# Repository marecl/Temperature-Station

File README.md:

# Temperature Station  
## I made this project for my father who needed to log activity of central heater  

Please use PCF8563_JSON version.  
I2C expander is ATmega board which will extend amount of sensors that can be connected (WIP).  

If there is Error[500] use another browser (8563 donsent work with Edge but DS32321 does idk why)  
	
		!!!TODO!!!  

	Main sketch:  
		1. Add SSL support (including login page)  
		2. WWW based updater  
		3. Automatic daylight saving  
		4. Encrypt WiFi password   
		5. Set date and time on the webpage  
		6. Save each file as JSON and show as CSV  
		7. SettingsGenerator for everything but sensors

	Czas.h library:  
		1. Return actual date and time as epoch  

	Hardware:   
		1. Make full-SMD version (without NodeMCU, just ESP-12E)

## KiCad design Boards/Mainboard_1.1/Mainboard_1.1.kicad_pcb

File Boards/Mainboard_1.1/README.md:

First version.
Single sided.
Requires retracing some SD lines which were connected to GPIO9&10.
No i2c breakout.

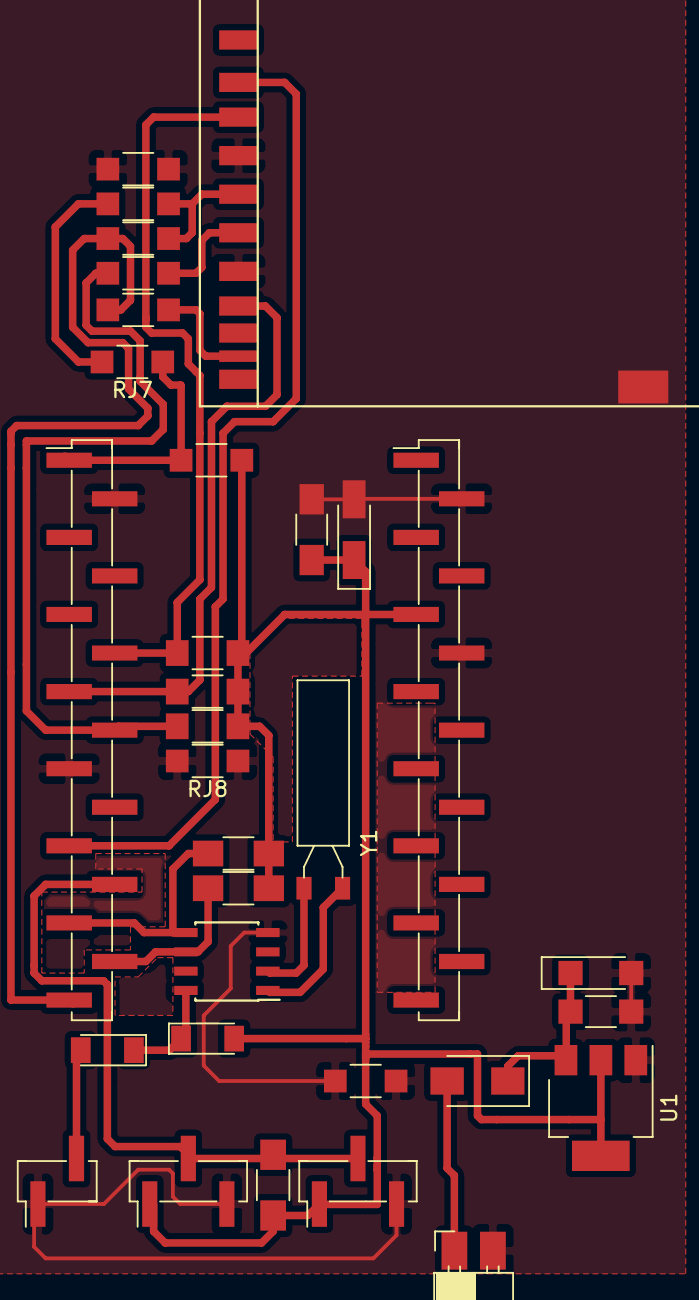
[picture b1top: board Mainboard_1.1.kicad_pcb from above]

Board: 2 copper layers, 32 parts (0 on the bottom side), 18 nets.

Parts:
C1, C3: 10nF; C_1206_HandSoldering
C2, C4: 10uF; CP_Tantalum_Case-A_EIA-3216-18_Hand
D1, D3: 1N4148; D_MiniMELF
D2: 1N4007; D_SMA
J1, J5: CONN_01X03; Pin_Header_Straight_1x03_Pitch2.54mm_SMD_Pin1Left
J2, J3: CONN_01X15; Pin_Header_Straight_1x15_Pitch2.54mm_SMD_Pin1Left
J4: SD_Card; SDCARD-STANDARD
J6: CONN_01X02; Pin_Header_Straight_1x02_Pitch2.54mm_SMD_Pin1Left
J7: CONN_01X02; Socket_Strip_Angled_1x02_Pitch2.54mm
R1, R2, R3, R4: 10k; R_1206_HandSoldering
R5, R6, R7: 4k7; R_1206_HandSoldering
RJ1, RJ2, RJ3, RJ4, RJ5, RJ6, RJ7, RJ8: 0; R_1206_HandSoldering
U1: LM1117-3.3; SOT-223-3Lead_TabPin2
U2: PCF8563; SOIC-8_3.9x4.9mm_Pitch1.27mm
Y1: Crystal; Crystal_AT310_d3.0mm_l10.0mm_Horizontal

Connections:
1wire: J1.2, J2.12, J5.2, R5.2
3V3: C3.1, C4.1, D1.2, J1.1, J2.1, J3.5, J4.4, J5.1, R1.1, R2.1, R3.1, R4.1, R5.1, R6.1, R7.1, RJ2.1, RJ2.2, RJ3.1, RJ3.2, RJ7.1, RJ7.2, U1.2
CS: J2.11, J4.1
GND: C1.2, C2.2, C3.2, C4.2, J1.3, J2.2, J2.9, J3.2, J3.6, J4.3, J4.6, J4.12, J5.3, J6.1, J7.2, RJ4.1, RJ4.2, RJ6.1, RJ6.2, RJ8.1, RJ8.2, U1.1, U2.4
MISO: J2.7, J4.7, R2.2
MOSI: J2.6, J4.2, R1.2
unnamed: C1.1, C2.1, D2.1, U1.3
unnamed: D1.1, D3.1, U2.8
unnamed: D2.2, J7.1
unnamed: D3.2, J6.2
unnamed: J2.8, R3.2, RJ1.1
unnamed: J4.10, RJ5.2
unnamed: U2.1, Y1.1
unnamed: U2.2, Y1.2
SCK: J4.5, RJ1.2
SCL: J2.14, R7.2, U2.6
SDA: J2.13, R6.2, U2.5
SD_D: J2.15, R4.2, RJ5.1

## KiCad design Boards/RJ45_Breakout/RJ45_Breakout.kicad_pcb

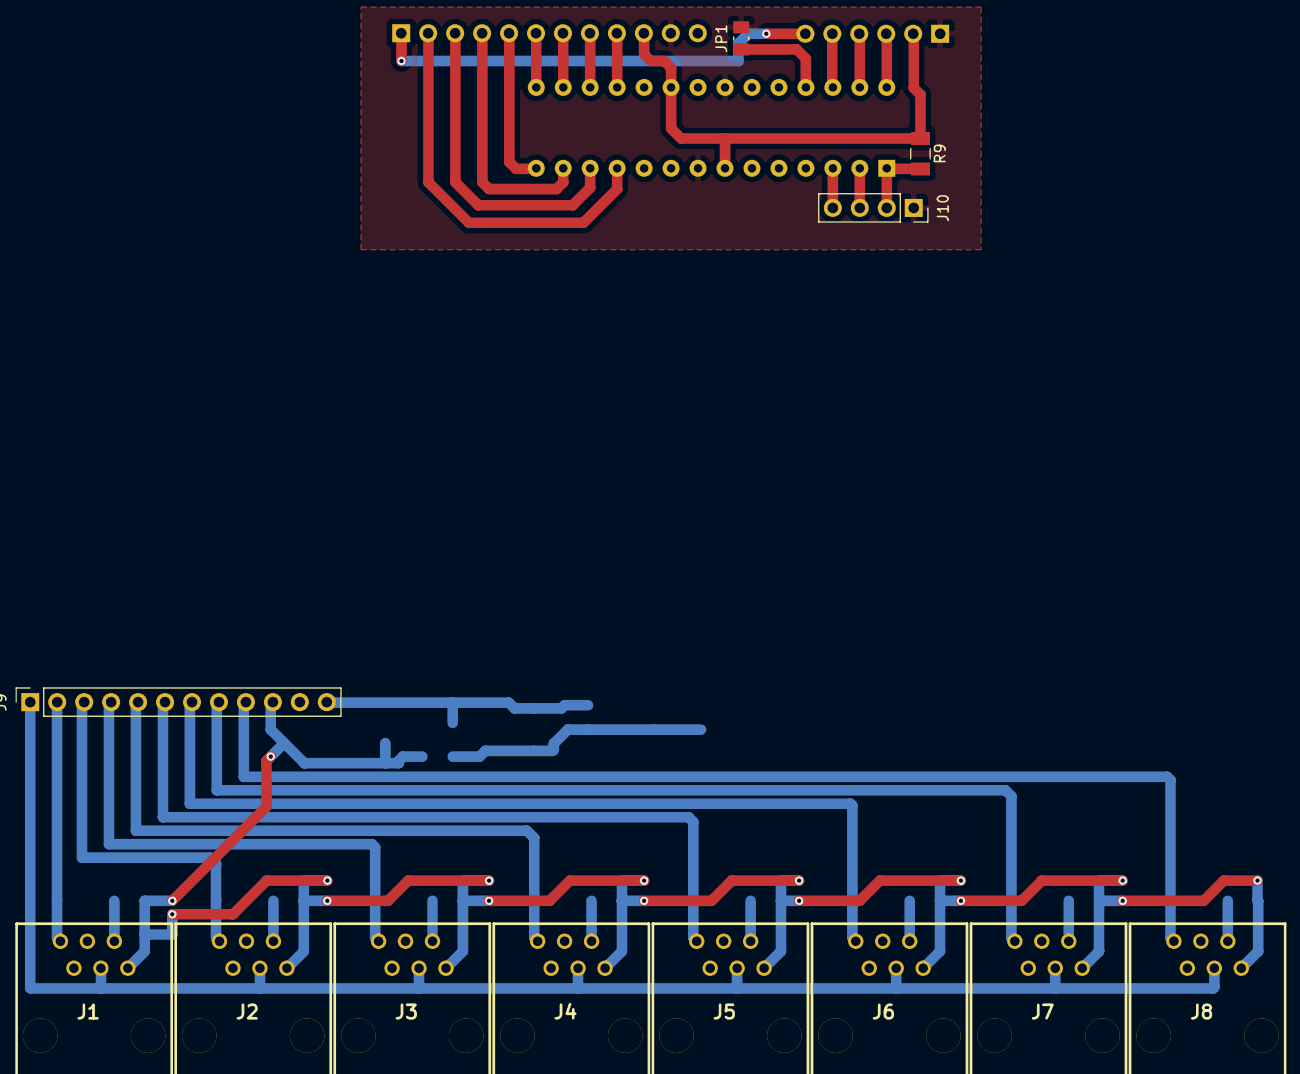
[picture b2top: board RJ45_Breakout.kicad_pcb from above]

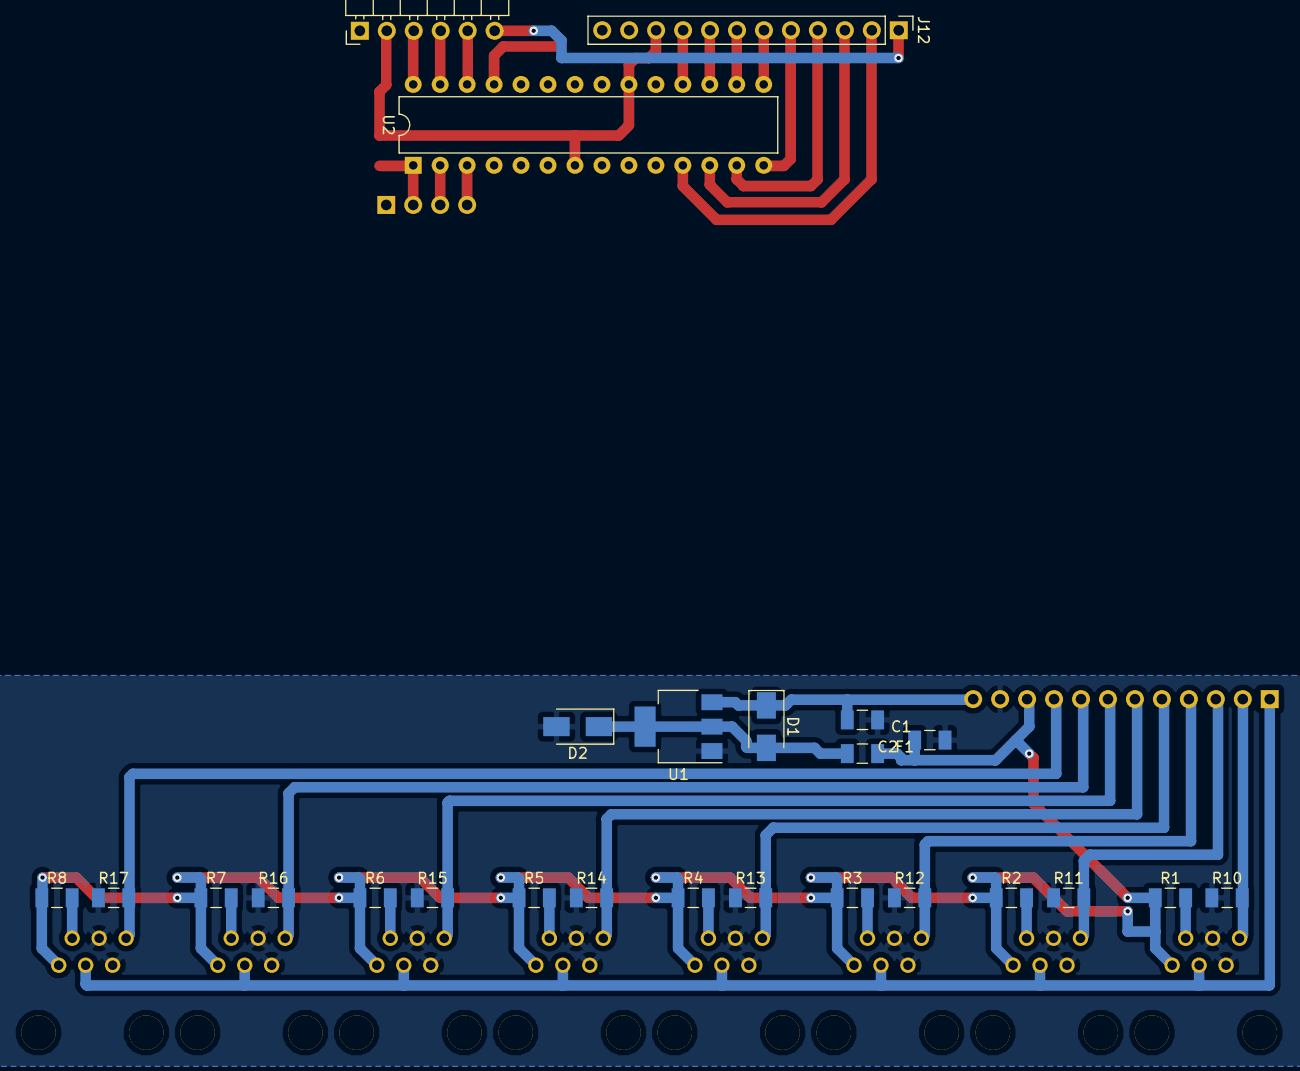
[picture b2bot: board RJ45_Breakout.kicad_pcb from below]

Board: 2 copper layers, 37 parts (25 on the bottom side), 28 nets.

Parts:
C1, C2: 100nF; C_1206_3216Metric
D1, D2: 1N4007; D_SMA
F1: 500mA; Fuse_1206_3216Metric
J1, J2, J3, J4, J5, J6, J7, J8: MHRJJ66NFRA
J9: Conn_01x12; PinSocket_1x12_P2.54mm_Vertical
J10: Prog; PinSocket_1x04_P2.54mm_Vertical
J11: Out; PinHeader_1x06_P2.54mm_Horizontal
J12: Flex; PinHeader_1x12_P2.54mm_Vertical
JP1: bypass1Wire; R_0805_2012Metric_Pad1.15x1.50mm_HandSolder
R1, R2, R3, R4, R5, R6, R7, R8: 4k7; R_1206_3216Metric
R9: 10k; R_1206_3216Metric
R10, R11, R12, R13, R14, R15, R16, R17: 33k; R_1206_3216Metric
U1: LM1117-3.3; SOT-223-3_TabPin2
U2: ATmega328-PU; DIP-28_W7.62mm

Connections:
1wire: J1.4, J2.4, J3.4, J4.4, J5.4, J6.4, J7.4, J8.4, J9.1, J11.6, J12.1
3V3: C2.1, F1.1, J1.6, J2.6, J3.6, J4.6, J5.6, J6.6, J7.6, J8.6, J9.10, J11.2, J12.10, R1.1, R2.1, R3.1, R4.1, R5.1, R6.1, R7.1, R8.1, R9.1, U2.7, U2.20
!Lock: J11.5, U2.26
GND: C1.2, C2.2, D2.2, J1.2, J1.3, J2.2, J2.3, J3.2, J3.3, J4.2, J4.3, J5.2, J5.3, J6.2, J6.3, J7.2, J7.3, J8.2, J8.3, J9.11, J10.1, J11.1, J12.11, JP1.2, R10.1, R11.1, R12.1, R13.1, R14.1, R15.1, R16.1, R17.1, U1.1, U2.8, U2.22
unnamed: D1.2, D2.1, F1.2, U1.2
unnamed: J1.5, R1.2
unnamed: J2.5, R2.2
unnamed: J3.5, R3.2
unnamed: J4.5, R4.2
unnamed: J5.5, R5.2
unnamed: J6.5, R6.2
unnamed: J7.5, R7.2
unnamed: J8.5, R8.2
unnamed: J10.2, R9.2, U2.1
unnamed: J10.3, U2.2
unnamed: J10.4, U2.3
unnamed: JP1.1, U2.25
SCL: J11.3, U2.28
SDA: J11.4, U2.27
Vin: C1.1, D1.1, J9.12, J12.12, U1.3
dht_0: J1.1, J9.2, J12.2, R10.2, U2.11
dht_1: J2.1, J9.3, J12.3, R11.2, U2.12
dht_2: J3.1, J9.4, J12.4, R12.2, U2.13
dht_3: J4.1, J9.5, J12.5, R13.2, U2.14
dht_4: J5.1, J9.6, J12.6, R14.2, U2.15
dht_5: J6.1, J9.7, J12.7, R15.2, U2.16
dht_6: J7.1, J9.8, J12.8, R16.2, U2.17
dht_7: J8.1, J9.9, J12.9, R17.2, U2.18

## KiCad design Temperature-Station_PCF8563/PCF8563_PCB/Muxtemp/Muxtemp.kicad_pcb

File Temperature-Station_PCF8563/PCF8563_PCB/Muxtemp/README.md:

Muxtemp board.

Default address is 0x10. If you don't like it - change it in sketch

!Lock - device is processing data (low state) or it's available (high)
1wire (jumpers closed) - master device will maintain 1wire circuit (Dosen't show specific port used)
1wire (jumpers open) - Muxtemp will maintain 1wire circuit like local sensors
SDA/SCL - I2C
3V3 - fused in case of short
3V3_L - Logic 3V3 (unfused)

Power supply header is used for external power regulator.

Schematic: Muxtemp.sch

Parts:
F1: 500mA; Fuse_1206_3216Metric
J1, J2, J3, J4, J5, J6, J7, J8: MHRJJ66NFRA; Manufacturer_Part_Number MHRJJ66NFRA
J9: ATmega Prog; PinHeader_1x04_P2.54mm_Vertical
J10: Conn; PinHeader_1x07_P2.54mm_Horizontal
J11: Power Supply; PinHeader_1x04_P2.54mm_Vertical
JP1, JP2, JP3, JP4, JP5, JP6, JP7, JP8, JP9: 1wireBypass; R_0612_1632Metric
R1, R2, R3, R4, R5, R6, R7, R8: 4k7; R_1206_3216Metric
R9, R10, R11, R12, R13, R14, R15, R16: 33k; R_1206_3216Metric
R17, R18: 100k; R_1206_3216Metric
R19: 10k; R_Axial_DIN0207_L6.3mm_D2.5mm_P10.16mm_Horizontal
U1: ATmega328P-AU; TQFP-32_7x7mm_P0.8mm

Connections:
1wire: J10.4, JP1.2, JP2.2, JP3.2, JP4.2, JP5.2, JP6.2, JP7.2, JP8.2, R17.2, U1.25 (PC2)
3V3: F1.1, J1.6, J2.6, J3.6, J4.6, J5.6, J6.6, J7.6, J8.6, R1.1, R2.1, R3.1, R4.1, R5.1, R6.1, R7.1, R8.1
3V3_L: F1.2, J10.6, J11.1, R19.1, U1.4 (VCC), U1.6 (VCC), U1.18 (AVCC)
GND: J1.2, J1.3, J2.2, J2.3, J3.2, J3.3, J4.2, J4.3, J5.2, J5.3, J6.2, J6.3, J7.2, J7.3, J8.2, J8.3, J9.1, J10.5, J11.2, JP9.2, R9.1, R10.1, R11.1, R12.1, R13.1, R14.1, R15.1, R16.1, R17.1, U1.3 (GND), U1.5 (GND), U1.21 (GND)
Lock: J10.3, U1.26 (PC3)
unnamed: J1.4, JP1.1
unnamed: J1.5, R1.2
unnamed: J2.4, JP2.1
unnamed: J2.5, R2.2
unnamed: J3.4, JP3.1
unnamed: J3.5, R3.2
unnamed: J4.4, JP4.1
unnamed: J4.5, R4.2
unnamed: J5.4, JP5.1
unnamed: J5.5, R5.2
unnamed: J6.4, JP6.1
unnamed: J6.5, R6.2
unnamed: J7.4, JP7.1
unnamed: J7.5, R7.2
unnamed: J8.4, JP8.1
unnamed: J8.5, R8.2
unnamed: J11.4, R18.1
unnamed: JP9.1, U1.24 (PC1)
unnamed: R19.2, U1.29 (~RESET~/PC6)
SCL: J10.1, U1.28 (PC5)
SDA: J10.2, U1.27 (PC4)
Vin: J10.7, J11.3, R18.2
dht_0: J1.1, J9.4, R9.2, U1.16 (PB4)
dht_1: J2.1, J9.3, R10.2, U1.15 (PB3)
dht_2: J3.1, J9.2, R11.2, U1.14 (PB2)
dht_3: J4.1, R12.2, U1.13 (PB1)
dht_4: J5.1, R13.2, U1.12 (PB0)
dht_5: J6.1, R14.2, U1.11 (PD7)
dht_6: J7.1, R15.2, U1.10 (PD6)
dht_7: J8.1, R16.2, U1.9 (PD5)

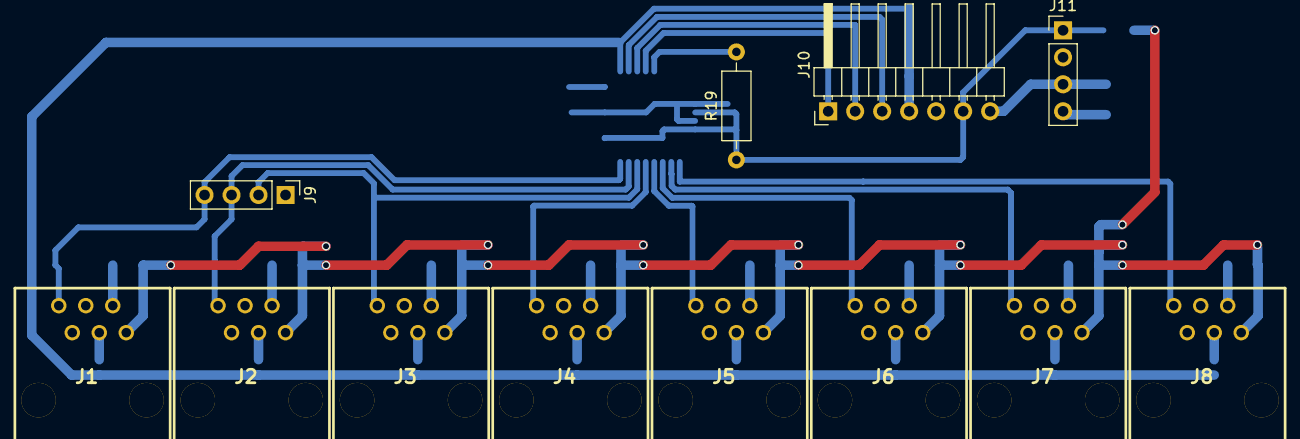
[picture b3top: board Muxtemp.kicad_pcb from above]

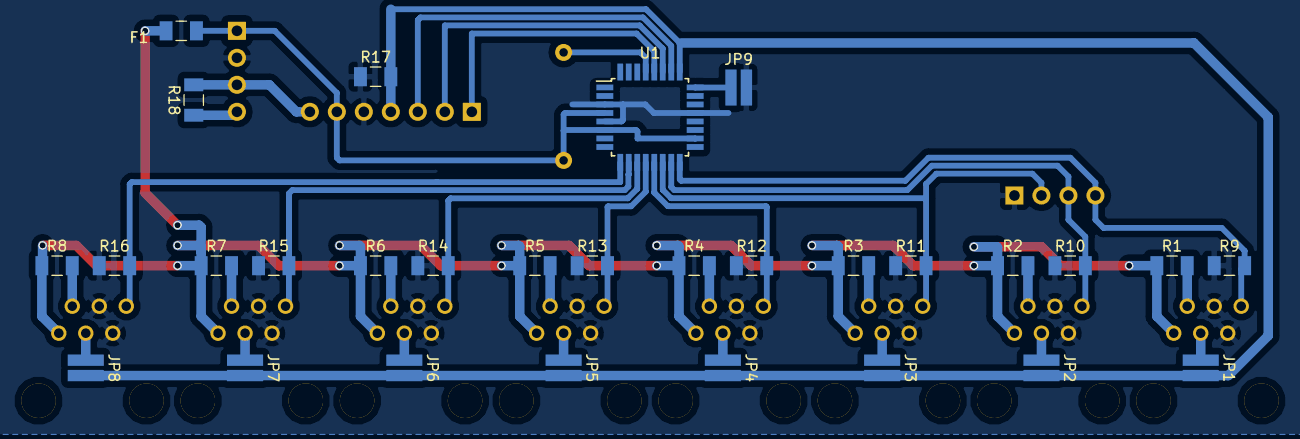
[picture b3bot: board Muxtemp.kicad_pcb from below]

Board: 2 copper layers, 41 parts (29 on the bottom side), 35 nets.

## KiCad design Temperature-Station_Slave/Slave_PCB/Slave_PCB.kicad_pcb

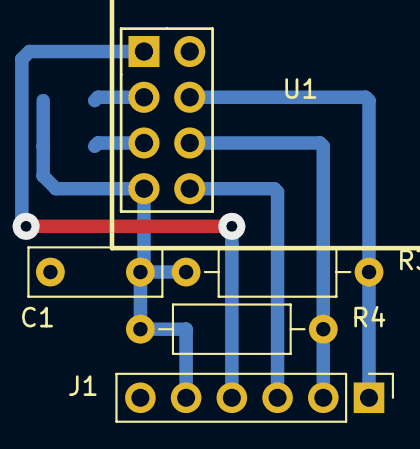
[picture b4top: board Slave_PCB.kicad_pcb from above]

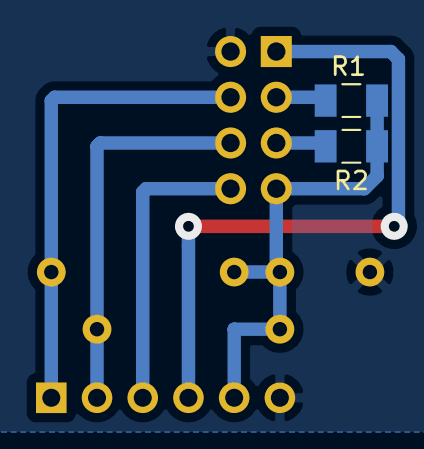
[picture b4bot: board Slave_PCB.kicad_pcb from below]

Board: 2 copper layers, 7 parts (2 on the bottom side), 8 nets.

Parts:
C1: 100nF; C_Rect_L7.2mm_W2.5mm_P5.00mm_FKS2_FKP2_MKS2_MKP2
J1: COM; PinHeader_1x06_P2.54mm_Vertical
R1, R2: 10k; R_1206_3216Metric
R3, R4: 4k7; R_Axial_DIN0207_L6.3mm_D2.5mm_P10.16mm_Horizontal
U1: ESP-01v090; ESP-01

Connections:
3V3: C1.1, J1.5, R1.1, R2.1, R3.2, R4.2, U1.7
GND: C1.2, J1.6, U1.2
unnamed: R1.2, U1.3
unnamed: R2.2, U1.5
SCL: J1.2, R4.1, U1.6
SDA: J1.1, R3.1, U1.4
hRX: J1.4, U1.1
hTX: J1.3, U1.8

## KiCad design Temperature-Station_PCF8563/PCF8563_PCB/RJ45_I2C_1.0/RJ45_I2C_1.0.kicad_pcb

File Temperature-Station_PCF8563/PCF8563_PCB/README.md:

Use legacy SDcard symbol from KiCad.
SDCARD.kicad_mod is footprint for PCB.

Created using KiCAD.

Mainboard_1.1 - early version. Obsolete.
Mainboard_2.0 - prototype. Never created.
Mainboard_3.0 - last version. Working.
RJ45_Breakout - early version of Muxtemp. Obsolete but working with Mainboard_3.0
Mainboard_Final - Muxtemp integrated into mainboard. To be tested.
Muxtemp - Muxtemp board. To be tested (probably will not due to limited resources)

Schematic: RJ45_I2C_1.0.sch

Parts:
J1: Conn_01x12; PinSocket_1x12_P2.54mm_Vertical
J2: Out; PinHeader_1x05_P2.54mm_Vertical
J3: Prog; PinSocket_1x04_P2.54mm_Vertical
JP1: bypass1Wire; R_0805_2012Metric_Pad1.15x1.50mm_HandSolder
R1: 10k; R_1206_3216Metric
U1: ATmega328-PU; DIP-28_W7.62mm

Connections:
1wire: J1.1, J2.5
3V3: J1.10, J2.2, R1.1, U1.7 (VCC), U1.20 (AVCC)
GND: J1.11, J2.1, J3.1, JP1.2, U1.8 (GND), U1.22 (GND)
unnamed: J3.2, R1.2, U1.1 (~RESET~/PC6)
unnamed: J3.3, U1.2 (PD0)
unnamed: J3.4, U1.3 (PD1)
unnamed: JP1.1, U1.26 (PC3)
SCL: J2.3, U1.28 (PC5)
SDA: J2.4, U1.27 (PC4)
Vin: J1.12
dht_0: J1.2, U1.11 (PD5)
dht_1: J1.3, U1.12 (PD6)
dht_2: J1.4, U1.13 (PD7)
dht_3: J1.5, U1.14 (PB0)
dht_4: J1.6, U1.15 (PB1)
dht_5: J1.7, U1.16 (PB2)
dht_6: J1.8, U1.17 (PB3)
dht_7: J1.9, U1.18 (PB4)

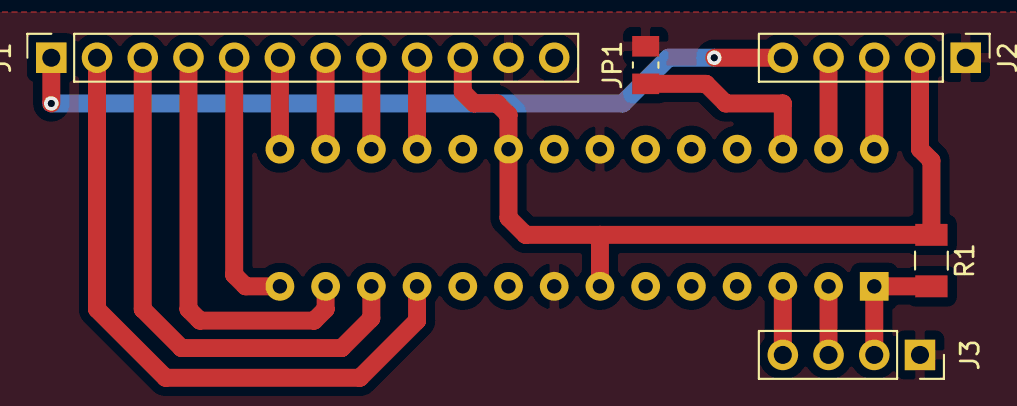
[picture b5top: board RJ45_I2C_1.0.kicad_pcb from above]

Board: 2 copper layers, 6 parts (1 on the bottom side), 17 nets.

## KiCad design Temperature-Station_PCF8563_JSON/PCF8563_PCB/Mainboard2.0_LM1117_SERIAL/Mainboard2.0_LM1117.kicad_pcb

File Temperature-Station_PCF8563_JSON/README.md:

# This version is getting all updates  

It's using single JSON (saved as text) file to store all settings.  

Features:  
	1. Single configuration file  
	2. (quite) Easy configuration 
	3. Stable

	Definitions:  
		* SETTINGS_FILE [name] - I don't think it needs explaination  
		* MAX_SENSORS (number) - how many sensors will be used (16 is enough I think)  

	SDfiles:  
		Copy index.htm to the root of SDcard.  
		Use SettingsGenerator to create settings file which is needed to run.  
		You can fill SETTINGS_BLANK.txt using SETTINGS_SAMPLE.txt or simply copy and rename sample file.  
		
	SETTINGS.TXT:  
		"sensor": this object stores sensor name and address. Address stored as decimal!  
				["sensor"][sensor number][0] - sensor name  
				["sensor"][sensor number][1-8] - sensor address as decimal  
		"valid_sensors": how many sensors are set (above)  
		"ip": IP settings  
			"mode": dhcp, static or dhcp_stat. The third one saves DHCP settings and changes itself to static for one-time IP configuration.  
			"ip": desired/obtained IP address  
			"gateway": gateway  
			"subnet": subnet mask  
		"wlan": table of many SSIDs and passphrases. Station will try to connect to every access point declared in file. Order of connecting is just as given.  
				If you don't want to use WiFi fill ssid and password with -1 (if filling settings manually)
		"saved_ap": number of access points saved in file.  
		"ntp_server": Self explainatory but don't use pools.  
		"use_ntp": self explainatory, probably going to mature this later  
		"timezone": also self explainatory. 
	
# Warning on first run! (workaround)   
If You need to get sensor addresses and You are generating settings for the first time:  
		1. Asked for name and address enter whatever you want    
		(write 000,000,000,000,000,000,000,000)
		2. Enter \quit.
		3. Configure network
			3.1. IP address will be saved to settings file  
		4. Connect to Your station [ip]/sensors   
		5. Remove 000,000(and so on) sensor and name sensors shown in table.  
		Checkbox checked - this sensor's name will be removed.  

SettingsGenerator has got validation mechanisms. They're working for me.  
When invalid address (sensor or IP) is entered it will ask you to write it again. Simple.  

Order of logged temperatures is just as order in file.  
If you change this file remember to rename your current log file.  
For logging changes will be applied immediately, but header will remain the same until new file is generated.  

	Known bug: I have no idea why, but when I put my board on power supply (dosen't matter if turned on or off) it's going nuts and loses time. Pretty strange, need to make another board.

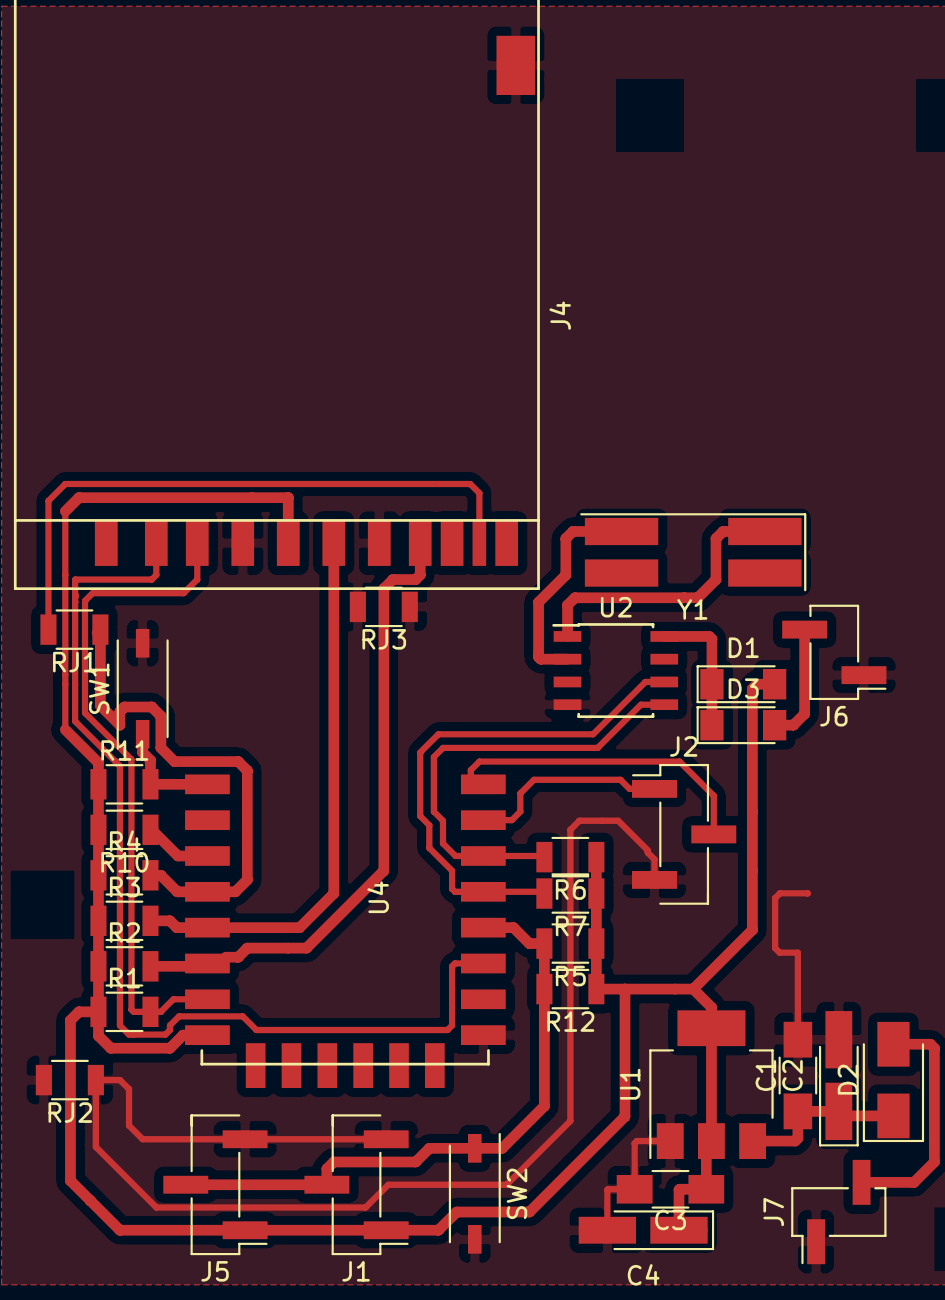
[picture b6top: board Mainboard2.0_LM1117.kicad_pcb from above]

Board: 2 copper layers, 32 parts (0 on the bottom side), 21 nets.

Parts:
C1, C3: 10nF; C_1206_HandSoldering
C2, C4: 10uF; CP_Tantalum_Case-A_EIA-3216-18_Hand
D1, D3: 1N4148; D_MiniMELF
D2: 1N4007; D_SMA
J1, J2, J5: CONN_01X03; Pin_Header_Straight_1x03_Pitch2.54mm_SMD_Pin1Left
J4: SD_Card; SDCARD-STANDARD
J6, J7: CONN_01X02; Pin_Header_Straight_1x02_Pitch2.54mm_SMD_Pin1Left
R1, R2, R3, R4: 10k; R_1206
R5, R6, R7: 4k7; R_1206
R10, R11, R12: 1k; R_1206
RJ1, RJ2, RJ3: 0; R_1206
SW1: RESET; SW_DIP_x1_W5.08mm_Slide_Copal_CHS-A
SW2: FLASH; SW_DIP_x1_W5.08mm_Slide_Copal_CHS-A
U1: LM1117-3.3; SOT-223-3Lead_TabPin2
U2: PCF8563; SOIC-8_3.9x4.9mm_Pitch1.27mm
U4: ESP-12E; ESP-12E_SMD
Y1: Crystal; Crystal_SMD_SeikoEpson_MC406-4pin_9.6x4.1mm

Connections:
1wire: J1.2, J5.2, R5.2, R12.2, SW2.1, U4.12
3V3: C3.1, C4.1, D1.2, J1.1, J4.4, J5.1, R1.1, R2.1, R3.1, R4.1, R5.1, R6.1, R7.1, R10.2, R11.1, R12.1, U1.2, U4.8
CS: J4.1, U4.11
GND: C1.2, C2.2, C3.2, C4.2, J1.3, J2.3, J4.3, J4.6, J4.12, J5.3, J6.1, J7.1, RJ2.1, RJ2.2, RJ3.1, RJ3.2, SW1.2, SW2.2, U1.1, U2.4, U4.9
GPIO4: R7.2, U2.6, U4.13
GPIO5: R6.2, U2.5, U4.14
GPIO12: J4.7, R2.2, U4.6
GPIO13: J4.2, R1.2, U4.7
GPIO14: J4.5, R3.2, U4.5
unnamed: C1.1, C2.1, D2.1, U1.3
unnamed: D1.1, D3.1, U2.8
unnamed: D2.2, J7.2
unnamed: D3.2, J6.2
unnamed: J4.10, RJ1.2
unnamed: R10.1, U4.3
unnamed: U2.1, Y1.1
unnamed: U2.2, Y1.2
RESET: R11.2, SW1.1, U4.1
Rx: J2.1, U4.15
SD_D: R4.2, RJ1.1, U4.4
Tx: J2.2, U4.16

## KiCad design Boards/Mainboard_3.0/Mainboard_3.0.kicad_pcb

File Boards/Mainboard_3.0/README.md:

Current version.
Dosent use NodeMCU (which was hard to set due to different board sizes and pins).
Two layers.
Prepared for external I2C devices (like more sensors or controllers).
Made to be compatible with ESP-12 breakout board.
Tested, 100% working.

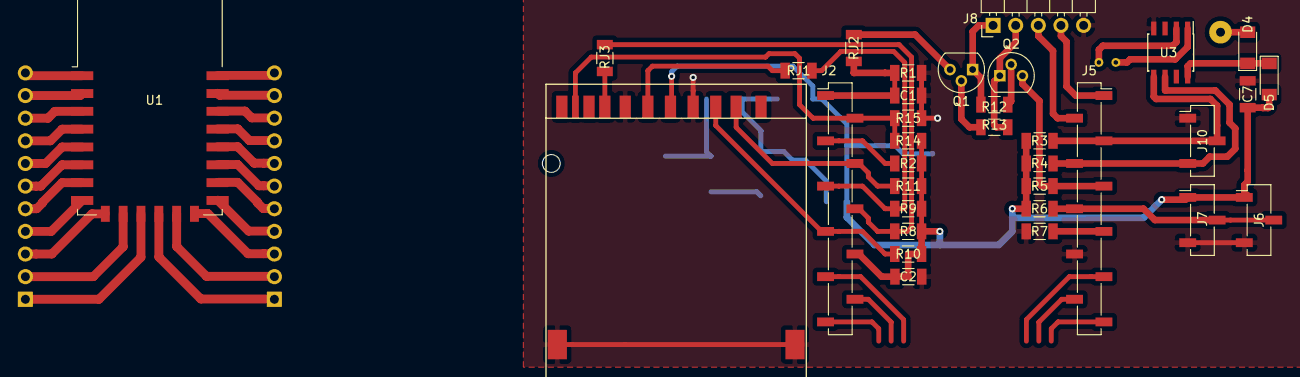
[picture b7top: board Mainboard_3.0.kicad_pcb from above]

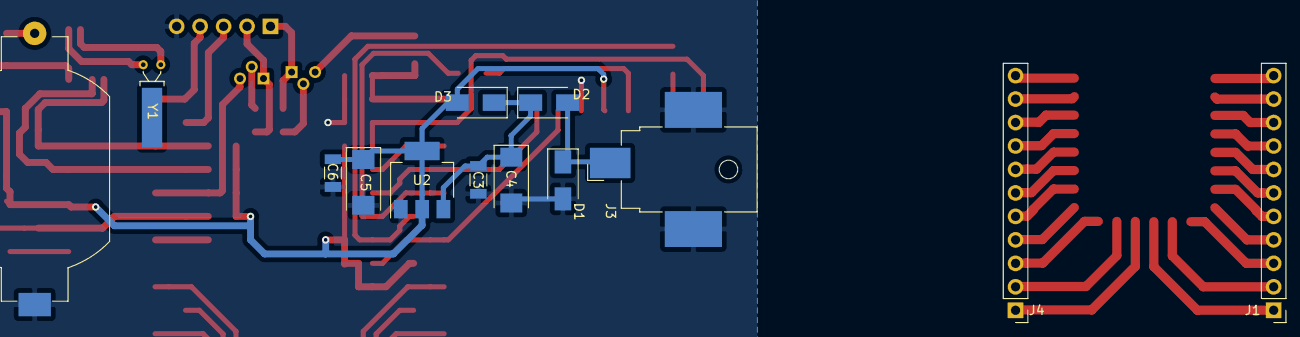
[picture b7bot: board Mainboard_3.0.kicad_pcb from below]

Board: 2 copper layers, 47 parts (13 on the bottom side), 51 nets.

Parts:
BT1: Battery_Cell; BatteryHolder_Keystone_1058_1x2032
C1, C2, C3, C6, C7: 100nF; C_1206_3216Metric
C4, C5: 10uF; CP_EIA-6032-28_Kemet-C
D1, D2, D3: 1N4007; D_SMA
D4, D5: 1N4148; D_MiniMELF
J1: Breakout_Left; PinHeader_1x11_P2.54mm_Vertical
J2: Socket_Left; PinSocket_1x11_P2.54mm_Vertical_SMD_Pin1Left
J3: Jack-DC; BarrelJack_CUI_PJ-036AH-SMT_Horizontal
J4: Breakout_Right; PinHeader_1x11_P2.54mm_Vertical
J5: Socket_Right; PinSocket_1x11_P2.54mm_Vertical_SMD_Pin1Right
J6: 1-Wire; PinSocket_1x03_P2.54mm_Vertical_SMD_Pin1Left
J7: sensor_internal; PinSocket_1x03_P2.54mm_Vertical_SMD_Pin1Left
J8: Prog; PinHeader_1x05_P2.54mm_Horizontal
J9: SD_Card; SD_Card_Receptacle
J10: I2C Breakout; PinSocket_1x03_P2.54mm_Vertical_SMD_Pin1Left
Q1, Q2: S8050; TO-92
R1, R2, R3, R4, R5, R6, R7, R15: 4k7; R_1206_3216Metric
R8, R9, R10, R11, R12, R13, R14: 10k; R_1206_3216Metric
RJ1, RJ2, RJ3: 0; R_1206_3216Metric
U1: ESP-12E
U2: LM1117-3.3; SOT-223-3_TabPin2
U3: PCF8563T; SOIC-8_3.9x4.9mm_P1.27mm
Y1: 32,768kHz; Crystal_C26-LF_D2.1mm_L6.5mm_Horizontal_1EP_style1

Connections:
3v3: C2.1, C5.1, C6.1, C7.1, D3.2, D5.2, J2.8, J6.1, J7.1, J9.4, R2.1, R3.1, R4.1, R5.1, R6.1, R8.1, R9.1, R10.1, R11.1, R14.1, U2.2
ADC: J2.2, J9.10, R14.2, R15.1
GND: BT1.2, C1.2, C2.2, C3.2, C4.2, C5.2, C6.2, C7.2, D1.2, J3.2, J3.3, J5.8, J6.3, J7.3, J8.5, J9.3, J9.6, J9.12, J9.13, J10.1, R1.1, R7.1, R15.2, U2.1, U3.4
GPIO0: J5.5, Q2.3, R5.2
GPIO2: J5.6, J6.2, J7.2, R6.2
GPIO4: J5.4, J10.3, R4.2, U3.6
GPIO5: J5.3, J10.2, R3.2, U3.5
GPIO12: J2.6, R8.2, RJ3.2
GPIO13: J2.7, J9.2, R10.2
GPIO14: J2.5, R9.2, RJ1.2
GPIO16: J2.4, J9.1, R11.2
unnamed: BT1.1, D4.2
unnamed: C3.1, C4.1, D2.1, D3.1, U2.3
unnamed: D1.1, D2.2, J3.1
unnamed: D4.1, D5.1, U3.8
unnamed: J1.1, U1.11
unnamed: J1.2, U1.10
unnamed: J1.3, U1.9
unnamed: J1.4, U1.8
unnamed: J1.5, U1.7
unnamed: J1.6, U1.6
unnamed: J1.7, U1.5
unnamed: J1.8, U1.4
unnamed: J1.9, U1.3
unnamed: J1.10, U1.2
unnamed: J1.11, U1.1
unnamed: J2.3, R2.2
unnamed: J4.1, U1.12
unnamed: J4.2, U1.13
unnamed: J4.3, U1.14
unnamed: J4.4, U1.15
unnamed: J4.5, U1.16
unnamed: J4.6, U1.17
unnamed: J4.7, U1.18
unnamed: J4.8, U1.19
unnamed: J4.9, U1.20
unnamed: J4.10, U1.21
unnamed: J4.11, U1.22
unnamed: J5.7, R7.2
unnamed: J8.1, Q1.1, R13.2
unnamed: J8.2, Q2.1, R12.2
unnamed: J9.5, RJ1.1
unnamed: J9.7, RJ3.1
unnamed: Q1.2, R12.1
unnamed: Q1.3, RJ2.1
unnamed: Q2.2, R13.1
unnamed: U3.1, Y1.1
unnamed: U3.2, Y1.2
RST: C1.1, J2.1, R1.2, RJ2.2
RX: J5.2, J8.3
TX: J5.1, J8.4

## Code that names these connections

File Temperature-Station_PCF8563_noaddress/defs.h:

/*
  #define SD_D D0 //GPIO16
  #define SDA D1 //GPIO5
  #define SCL D2 //GPIO4
  #define OW_PORT D3 //GPIO0
  #define SD_CS D4 //GPIO2
*/

#define SD_D A0
#define SDA 5
#define SCL 4
#define MUX_LOCK 2
#define SD_CS 16

static const uint8_t x509[] PROGMEM = {
#include "x509.h"
};
static const uint8_t rsakey[] PROGMEM = {
#include "key.h"
};

void saveJson(JsonObject& toSave, const char* _f) {
  if (!toSave.success()) return;
  if (SD.exists(_f)) SD.remove(_f);
  File root = SD.open(_f, FILE_WRITE);
  toSave.printTo(root);
  root.flush();
  root.close();
  return void();
}

String printDateTime(Czas& timeobj) {
  char datestring[20];
  snprintf_P(datestring, 20,
             PSTR("%02u/%02u/%04u;%02u:%02u"),
             timeobj.day(),
             timeobj.month(),
             timeobj.year(),
             timeobj.hour(),
             timeobj.minute());
  return datestring;
}

void refreshSensors(Muxtemp* _s, const char* _n) {
  DynamicJsonBuffer jsonBuffer(350);
  File root;
  if (!SD.exists(_n)) {
    Serial.println("no file yo");
    root = SD.open(_n, FILE_WRITE);
    root.print(F("{\"remote\":[],\"local\":[]}"));
    root.flush();
    root.close();
  }
  root = SD.open(_n);

  JsonObject& nSet = jsonBuffer.parseObject(root);
  root.close();
  JsonArray& _l = nSet["local"];

  int8_t dif = _s->getCount() - _l.size();
  if (dif > 0) {
    for (uint8_t z = 0; z < dif; z++)
      _l.add("Port_" + String(_l.size() + 1));
    saveJson(nSet, _n);
  }
  _s->getPorts();
  return void();
}

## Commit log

2017-06-02 :circus_tent: Added .gitattributes & .gitignore files
2017-06-02 Initial commit
    Lots of things done, more to do.
    Works fine unless you want to use advanced options.
    Documentation planned in the future.
2017-06-03 Fixes
    Added static/dhcp option for obtaining IP address
    Little changes to code
2017-06-05 DS3231 addition
2017-06-06 Fixes
    Fixed editing, saving and uploading documents to server
    Minor code changes
    Minor board changes
2017-06-10 Working on templates
    Dear future me: do it.
    Dear githubbers: convert address from file to byte[8] table
2017-06-17 Mainboard changes
2017-06-17 Finishing templates
2017-06-18 templates
    Fixed template
    TODO: get temperature from device using table row number (order defined
    in template.txt)
2017-06-19 Things got better
    Added templates
    Improved method of logging
    Minor changes in board
2017-06-20 Some things fixed
    Removed test sketches
    Working on JSON as config
    Some bugs fixed
    Modified IPconfig sketch to take ssid and pass from compiled sketch, not
    file on SDcard so it's easier to use.
2017-06-21 JSON support added
    Now PCF8563 version is working with JSON configs. Less files, but
    responsibility is great.
    Works well as far, but the goal is removing vars containing addresses,
    sensor names and reading JSON directly from SDcard.
2017-06-26 Something with JSON + something
    Cleaned up things
    Changed SETTINGS.TXT internal structure
    Added my own library for PCF8563 (more clear and stuff)
    Minor improvements
2017-06-26 Fixes
    Fixed opening files from archive file tree
    Idk HOW IT WAS CREATING NEW FILES before. Now everything is 100% legit.
    Still many things to do.
2017-06-27 Application, configuration
    See changes in README
    Added program to create settings.txt
    Added GET url (/sensors) to list all connected sensors (WIP)
    I forgot what else.
2017-07-01 Fixes and additions
    Splitted README files
    Modified SettingsGenerator
    Added "backup access points" feature on boot
    Fixed midnight bug
2017-07-01 Formatted README after unsuccesful merge
2017-07-03 SettingsGenerator update
    Added validating addresses in SettingsGenerator
    Modified LM1117 board (SOT instead of DPAK voltage stabiliser)
    Something I forgot
2017-07-08 PCB work
    Started working on full SMD version. Update KiCAD library before opening
    this one.
    Modified code and moved clock settings to JSON (needs update!) - I must
    upload new JSON and SettingsGenerator.
    Set all strings to flash memory
2017-07-09 PCB work
    Need to remove 1.1 files from 2.0 folder
    Fixed component enumeration so PCB rework will be easier
    Still need to finish new PCB
2017-07-15 Minor code changes
    Little cleanup
    Cosmetic changes
    Added keywords for Czas.h library and moved to it's own directory (otherwise keywords won't work)
    Removed unnescesary crap I forgot to remove earlier
    Updated description in README for PCF8563_JSON
    Updated SettingsGenerator for newest JSON
2017-07-16 Updates
    Added new IP obtain mode
    Changed PC program name
    Fixed compilator warnings
    Removed support for DHCP.txt file
    Czas.h: added function to compare given epoch to current date and time
2017-07-25 SMD board complete
    Full SMD board is complete - needs to be tested though. Looks kinda awful, large SD card slot is taking lots of space.
2017-09-20 Updates
    Ported DS3231 to JSON
2017-09-20 Clean
2017-10-02 DS3231 update
    Change sensor names through /sensors
2017-10-04 DS3231 update
    Auto adding sensors
    Can remove unplugged sensors
    Auto-add freshly connected
    TODO:
    Fix removing sensors
2017-10-05 PCF8563&DS3231 Update
    Both versions have the same features (and bugs)
    Reworked NTP time setting
    Fixed sensor removing (kind of)
    Slight memory optimization
    Automatic redirection after sensor manipulation
    Moved everything I could to FLASH instead of RAM memory.
2017-11-02 Updates
    Updated both versions
    Added online updater
    Minor cosmetic changes
    Saving DHCP settings restored
    Added authentication (still no HTTPS/TLS/SSL tho)
    Moved as many Strings as possible to Flash memory to free RAM
2018-01-23 Updates
    Reduced size of variables
    Settings file protected by code (not shown in site)
    Added button for sensor settings
    Files read only (webpage)
    Changed log file format (dynamic sensors friendly)
    Fixed bug where watchdog resets mcu when entering password
2018-02-22 Update
    Czas:
    Convert date to epoch (1-1-2000)
    Station:
    Config file in SPIFFS
    Web configuration
    Sensors file on SDcard
2018-04-23 Large updates
    SSL website (need to generate your own key.h and x509.h using script in ESP examples)
    Online config (without time settings yet)
    New board (3.0)
    WIP sensor settings (/sensors, removing temporarily disabled)
    Added slave devices (need low level configuration at the moment)
    Working on self-AP when there is no WiFi connection
2018-05-08 Little update
    Slave device can be configured (WIP)
    Working on expansion board (WIP)
2018-05-11 Updates
    Added slave board with library (Muxtemp) - DHT11/21/22 sensors
2018-05-23 Added external boards
    Added RJ45 breakout board which will need specifically prepared cable
    Added RJ45 independent I2C extension board (WIP)
    Documentation coming soon
2018-05-27 Updated boards and sketches
    Boards:
    Sandwich-like layout so you can connect directly do DHT sensors or use i2c expansion (8 slots).
    Boards support 1wire, DHT11/21/22 sensors and require custom wiring.
    Reduced size of boards
    Sketch:
    Hermetized settings (no way to read passwords)
2018-06-01 Muxtemp update
    Fixed begin()
    Removed function that only read ports (now it will only probe&read)
    Fixed typo (requesting fixed number of devices even if real amount is different)
    TODO: 1wire connection
2018-06-03 Muxtemp update
    1wire option added
    Working in bypass or local mode (if master can use 1wire it will NOT use 1wire devices)
    Example shows more info
2018-06-10 Large update
    Muxtemp:
    Optimized timing
    Added library.properies
    No compiler warnings
    Czas:
    No compiler warnings
2018-06-19 Update
    Halfway through
    Preparing to make very dumb version (different branch)
2018-07-08 Small updates
    Czas: added option to validate dat/time
    Muxtemp: added software lock placed by refresh() due to slow DHT sensors (going to be changed in next I2C breakout)
    More changes coming soon
2018-07-09 Cleaned boards up
    Merged RJ45_I2C with RJ45_Breakout into one schematic
    Added fully-integrated Muxtemp board
    Started working on Mainboard+Muxtemp board
    Settings page (html) is now functional. Backend WIP.
    SettingsHandler(PCF8563) is now cleaned up a bit, added optional define to include debug interface
    Added option to configure OTA updater as well as WebUpdater
2018-07-13 Optimizations and updates
    PCF8563:
    Added non-address version (sensor dosen't override port name)
    Finished settings
    Index and settings are stored in sketch, not SD-card
    Minor optimization (migrate to const char* instead of string)
    Temporarily disabled remote devices
2019-04-30 Updates
    Muxtemp:
    Library controls lock line entirely
    Temperature-Station DS3231:
    Prepared to use HTTPS
    Moved config to SPIFFS
    Moved webpages to SPIFFS
2019-05-11 Backend rebuild
    Changing structure of webserver
    Added cookie based authentication
    Moved from HTTPUpdater to ArduinoOTA
    Added CommonUtils to let backend interact with main loop
2019-09-04 Updates and stuff
    Added nonaddressable version for working with muxtemp
    Updates
    Crypto
    I'm lost, it's been over a year
2020-10-21 gerber
